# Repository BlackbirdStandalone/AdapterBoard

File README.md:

# Honda CBR1100XX Super Blackbird - Wiring harness adapter board

This project incorporates a printed circuit board design that allows you to connect from the OEM Honda CBR1100XX Blackbird wiring harness to your stand-alone ECU of choice.
This adapter board specifically targets the early 2000's model EFI Honda Blackbird.

In my case, it is an Australian 2002 model.

The OEM Keihin ECU contains two groups of 22 connector pins that mate with bikes wiring harness. The harness side contains the two connectors (black and light gray) that the ECU mates with. These 22-pin connectors are proprietary and are located underneath the seat at the rear of the motorcycle.

This PCB design provides a means of conveniently interfacing with the existing 22-pin connector to your specific standalone ECU of choice without having to sever the existing wiring harness.
A custom wiring harness can then be separately built to interface to the stand alone ECU via standard Molex connectors numbered at the top of the board.<br/> The benefit of such an interface board also allows you to revert to the original Keihin ECU if you so wish since it allows the bikes wiring harness to remain undisturbed.</BR>
Note: This will only be the case if the camshaft 3-tooth trigger wheel is also left undisturbed.

Fitment to a motorcycle will require the construction of two PCB's. An example of two completed boards are shown below together with its fitment to the existing wiring harness in place of the Keihin ECU.

Note: This project is in its early stages, so does not discuss packaging or sealing of the boards from the elements at this stage. It is evolutionary in nature and will attempt to improve shortcomings over time as new ideas come to light.

</BR>

### Extra Notes
As of this current version (v0.2b), the 22 x round gold-plated pin connectors on the lower half of the board are the closest match I could find as a replacement to the stock Keihin pins.</br>
The stock Keihin pins are 1.0mm wide and 0.7mm tall, therefore a rectangular pin. The replacement I have used is a 1.0mm round style pin. It fits into the harness side very snug. The search for a perfect pin match will continue for future boards revisions.

The last picture displays the Honda/Keihin side of the main bikes wiring harness. It is important that the receptacle (receiver side) is correctly mated with the pins on the PCB since it is easy to mis-align. The area of entry is shown in red. Therefore care must be taken with the pin alignment as the boards are plugged into the black and gray harness side connectors on the bike. The connection will be on the tight side due to the 1.0mm round pins, but they will work.

The pin spacings on the Keihin 22-way connector are 8.5mm in the vertical and 5.8mm horizontally.

The upper half of the board contains a series of 6 x 4-way Molex connectors. The connectors are part of the 'Mini Fit Jnr' family of Molex connectors. The example shown above uses automotive 20 AWG wire. The choice to use many smaller connectors rather than a single 24 way connector was mainly due to stock availability. The 4-way connectors are very common.

</BR>

### Project Details

<table border="1">

<tr> 
<td width="20%">
<strong><u>Current Revision</u></strong>
</td>
<td width="60%">
<strong><u>Date</u></strong>
</td>
<td width="20%">
<strong><u>Author</u></strong>
</td>
</tr>

<tr>
<td width="20%">
v0.2b
</td>
<td width="60%">
May 2026
</td>
<td width="20%">
Alex Kiaos
</td>
</tr>

</table>

</BR>

This project has been designed in Kicad 6.0.11 under linux and is licenced under the CERN Open Hardware Licence Version 2 - Strongly Reciprocal (CERN-OHL-S).</br></br>

The directory structure of this project is as follows:

<table border="1">

<tr> 
<td width="20%">
<strong><u>Directory</u></strong>
</td>
<td width="80%">
<strong><u>Description</u></strong>
</td>

</tr>

<tr>
<td width="20%">
BOM
</td>
<td width="80%">
Bill of materials
</td>
</tr>

<tr>
<td width="20%">
datasheets
</td>
<td width="80%">
Data sheets for pins and connectors
</td>
</tr>

<tr>
<td width="20%">
images
</td>
<td width="80%">
Various images, pictures, board renditions
</td>
</tr>

<tr>
<td width="20%">
kicad
</td>
<td width="80%">
The main kicad project folder.<br>
This contains the project itself (uses kicad 6.0.11)</br>
The main project file is 'CBR_AdapterBoard.kicad_pro' found under</br>'/pcb/kicad/CBR_AdapterBoard'.</br></br>
Gerber files can be found as a group of 9 individual files under the 'gerbers' folder or as a single zipped file under the 'gerber_zipped' folder for uploading to a PCB house for manufacture.</br></br>
The 'CustomLibrary' folder contains the custom symbols and footprints used in the project.
</td>

</table>

</br>

After cloning the repository and opening the project for the first time, you may need to set up the symbol and footprint library paths.

To setup the symbols library, in the menu:<br>
<pre><i>Preferences -> Manage Symbol Libraries</i><br>
  Then in the 2nd tab under 'Project specific libraries' add the following:<br>
Nickname: <b>Blackbird</b><br>
Library Path: <b>${KIPRJMOD}/../CustomLibrary/symbols/Blackbird_symbols.kicad_sym</b><br>
</pre>
<br><br>

To setup the footprint library, in the menu:<br>
<pre><i>Preferences -> Manage Footprint Libraries</i><br>
  Then in the 2nd tab under 'Project specific libraries' add the following<br>
Nickname: <b>Blackbird</b><br>
Library Path: <b>${KIPRJMOD}/../CustomLibrary/footprints/</b><br>
</pre>
<br>

# Relevant links

### PCBWay
To visit the PCBWay project and/or place an [order](https://www.pcbway.com/project/shareproject/Honda_CBR1100XX_Super_Blackbird_ECU_adapter_board_for_a_standalone_ECU_a730cd35.html).

### Wiring Harness & Pinouts
To see the ECU pin-out details, refer to the latest pdf file at:
[Wiring Harness Pinout diagram](https://github.com/BlackbirdStandalone/Documentation/tree/main/wiring).

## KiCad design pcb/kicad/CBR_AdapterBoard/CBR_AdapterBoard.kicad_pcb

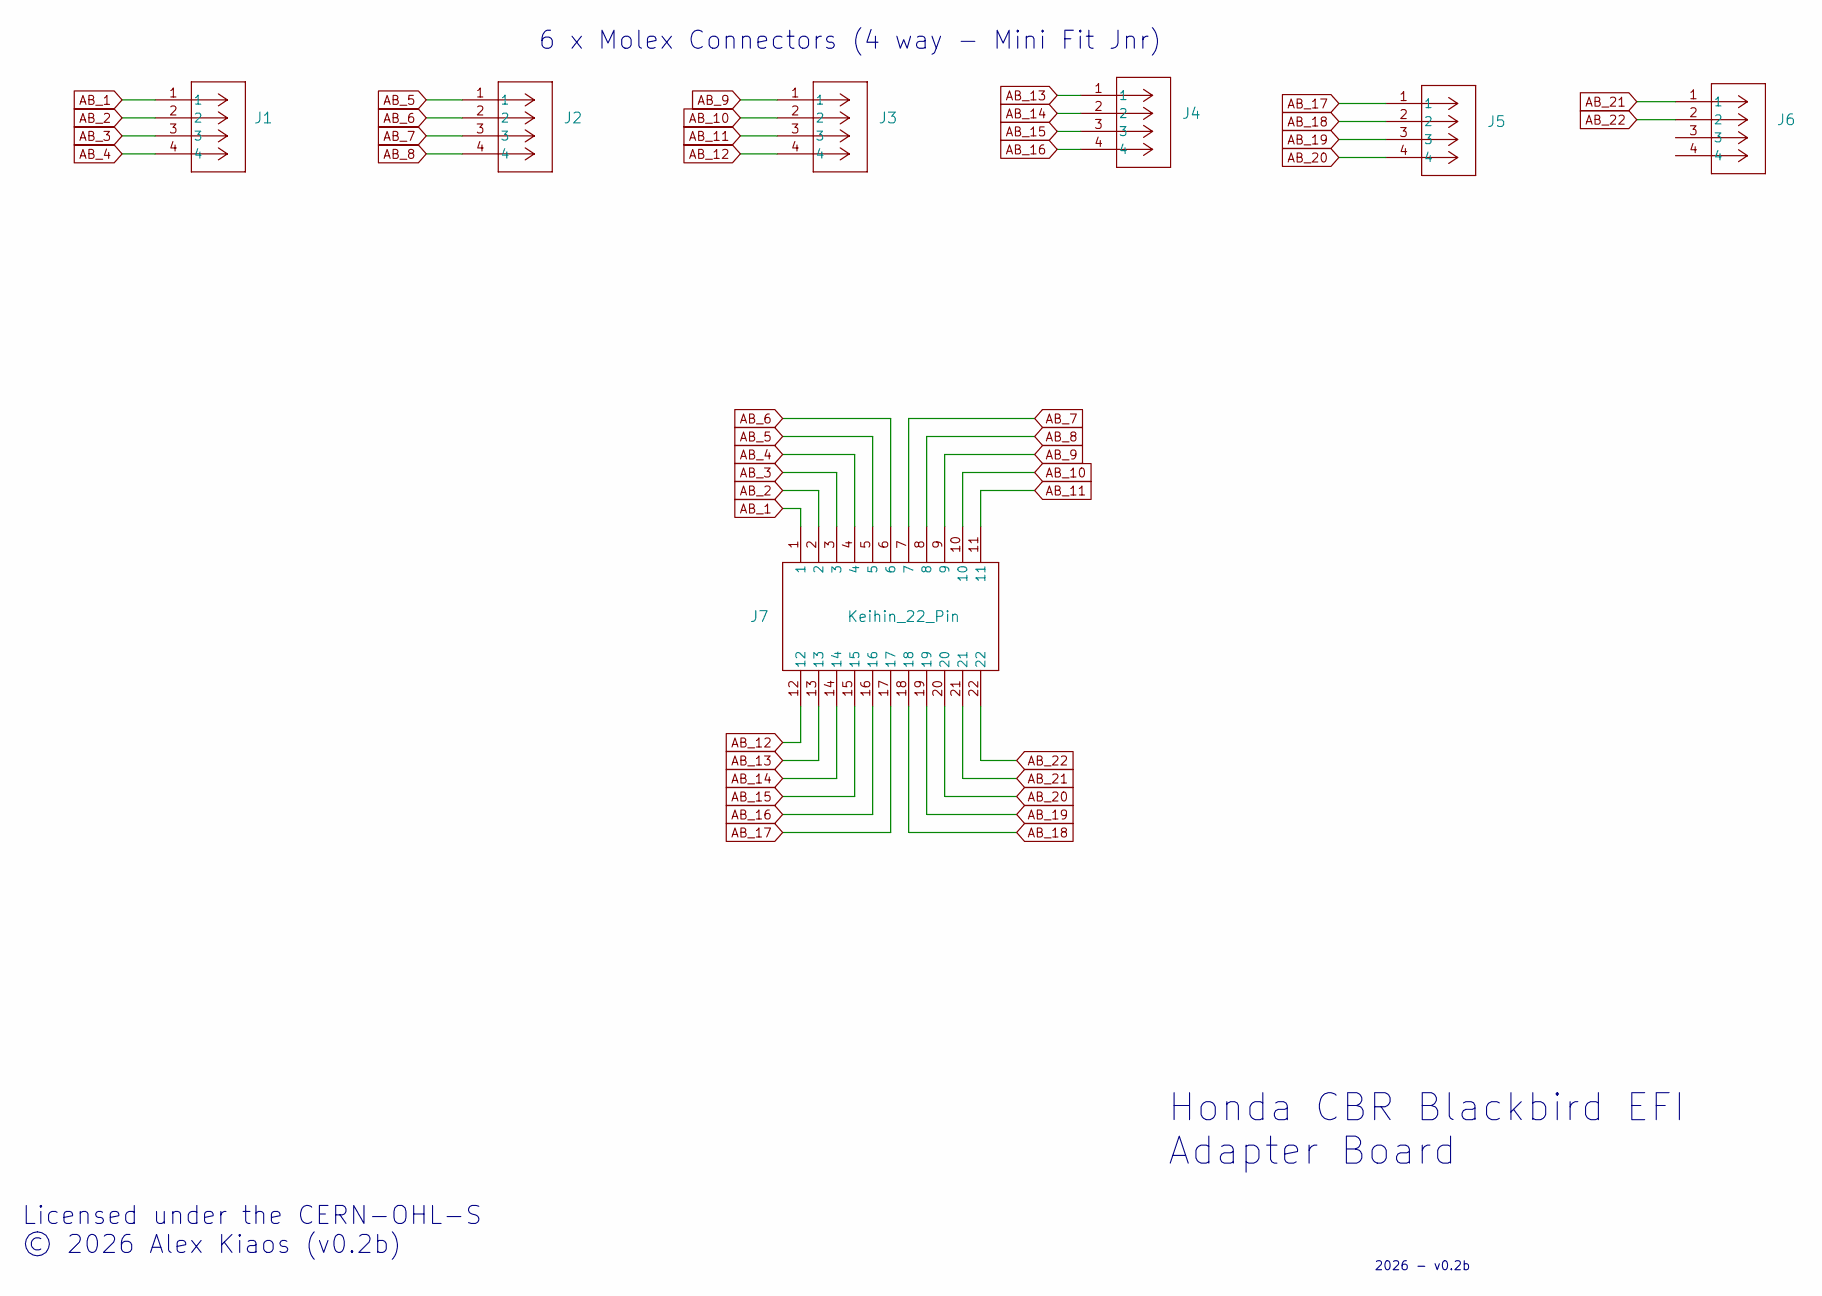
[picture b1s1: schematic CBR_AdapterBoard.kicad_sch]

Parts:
J1, J2, J3, J4, J5, J6: 2125201004; 4-Way-Molex_Connector-MiniFit-JNR
J7: Keihin_22_Pin; Blackbird_22_pin_keihin

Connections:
AB_1: J1.1, J7.1
AB_2: J1.2, J7.2
AB_3: J1.3, J7.3
AB_4: J1.4, J7.4
AB_5: J2.1, J7.5
AB_6: J2.2, J7.6
AB_7: J2.3, J7.7
AB_8: J2.4, J7.8
AB_9: J3.1, J7.9
AB_10: J3.2, J7.10
AB_11: J3.3, J7.11
AB_12: J3.4, J7.12
AB_13: J4.1, J7.13
AB_14: J4.2, J7.14
AB_15: J4.3, J7.15
AB_16: J4.4, J7.16
AB_17: J5.1, J7.17
AB_18: J5.2, J7.18
AB_19: J5.3, J7.19
AB_20: J5.4, J7.20
AB_21: J6.1, J7.21
AB_22: J6.2, J7.22

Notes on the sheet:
Honda CBR Blackbird EFI Adapter Board
6 x Molex Connectors (4 way - Mini Fit Jnr)
Licensed under the CERN-OHL-S © 2026 Alex Kiaos (v0.2b)
2026 - v0.2b

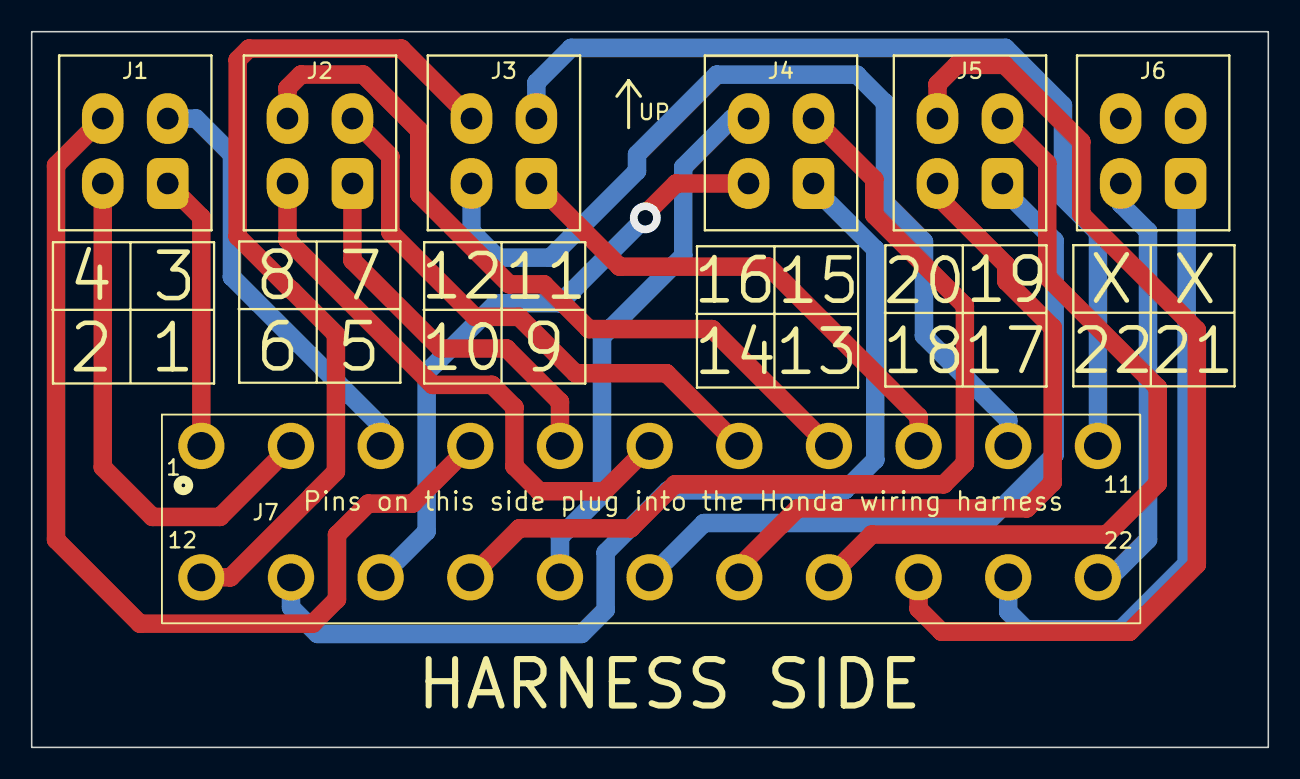
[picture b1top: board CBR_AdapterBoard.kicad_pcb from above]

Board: 2 copper layers, 80.0 x 46.3 mm, 7 parts (0 on the bottom side), 22 nets.

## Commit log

2026-01-09 - Added comments
2026-01-09 - Adding directories
2026-01-09 - Interim checkin.
2026-01-09 - Adding images directory
2026-01-09 - Structuring directories.
2026-01-10 - readme.md update
2026-01-10 - Adding symbols & footprint directories.
2026-01-10 - Adding gerbers.
2026-01-11 - File corrections.
2026-01-11 - Updated readme.md
2026-01-11 - BOM spreadsheet corrections.
2026-01-12 - Update readme
2026-01-12 - image file update
2026-01-13 - Update BOM
2026-01-14 - Added to readme
2026-01-14 - readme fix
2026-05-14 - Update directory structure
